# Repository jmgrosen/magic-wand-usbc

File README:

the proprietary charger for the rechargeable magic wand is pretty annoying, isn't it? this is a dongle that lets you charge it with any 15W USB-C charger instead!

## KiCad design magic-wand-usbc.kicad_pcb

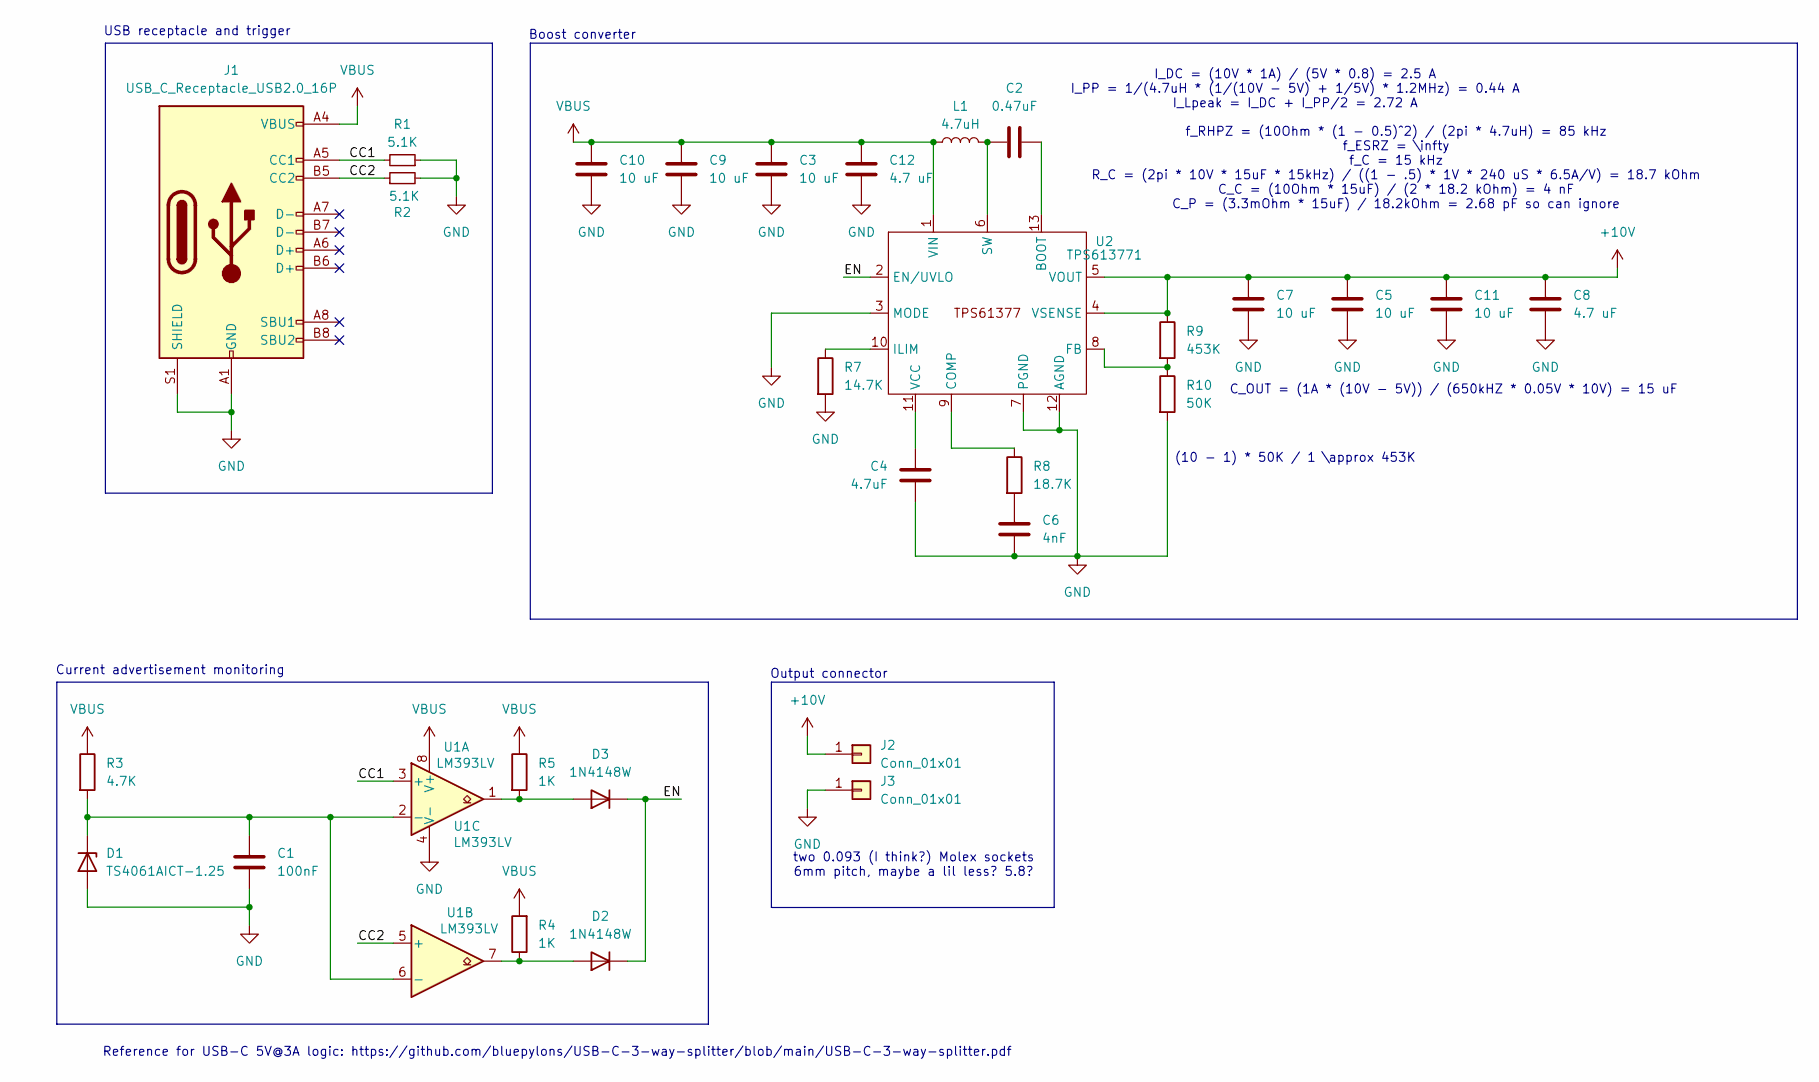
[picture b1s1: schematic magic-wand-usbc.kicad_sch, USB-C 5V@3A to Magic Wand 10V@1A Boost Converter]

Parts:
C1: 100nF; C_0402_1005Metric; DigiKey Part Number 1276-1043-1-ND
C2: 0.47uF; C_0402_1005Metric; DigiKey Part Number 311-1735-1-ND
C3, C5, C7, C9, C10, C11: 10 uF; C_0805_2012Metric; DigiKey Part Number 490-10514-1-ND
C4: 4.7uF; C_0402_1005Metric; DigiKey Part Number 490-GRM155C61E475ME15DCT-ND
C6: 4nF; C_0402_1005Metric; DigiKey Part Number 490-GCM155R71H392KA37DCT-ND
C8, C12: 4.7 uF; C_0402_1005Metric; DigiKey Part Number 490-GRM155C61E475ME15DCT-ND
D1: TS4061AICT-1.25; SOT-323_SC-70; DigiKey Part Number 497-15220-1-ND
D2, D3: 1N4148W; D_SOD-523; DigiKey Part Number 1N4148WTDICT-ND
J1: USB_C_Receptacle_USB2.0_16P; USB_C_Receptacle_GCT_USB4105-xx-A_16P_TopMnt_Horizontal; DigiKey Part Number 2073-USB4105-GF-ACT-ND
J2, J3: Conn_01x01; Molex_Socket_Janky
L1: 4.7uH; IND_SRP4030FA_BRN; Part Number SRP4030FA-4R7M; DigiKey Part Number SRP4030FA-4R7MCT-ND
R1, R2: 5.1K; R_0402_1005Metric; DigiKey Part Number 13-RC0402FR-135K1LCT-ND
R3: 4.7K; R_0402_1005Metric; DigiKey Part Number 311-4.7KLRCT-ND
R4, R5: 1K; R_0402_1005Metric; DigiKey Part Number 311-1.00KLRCT-ND
R7: 14.7K; R_0402_1005Metric; DigiKey Part Number YAG5262CT-ND
R8: 18.7K; R_0402_1005Metric; DigiKey Part Number YAG3018CT-ND
R9: 453K; R_0402_1005Metric; DigiKey Part Number YAG3164CT-ND
R10: 50K; R_0402_1005Metric; DigiKey Part Number 541-CRCW040250K0FKEDCT-ND
U1: LM393LV; WSON8_DSG_TEX; Part Number LM393LVDSGR; DigiKey Part Number 296-LM393LVDSGRCT-ND
U2: TPS613771; TPS61377-VQFN-HR13; DigiKey Part Number 296-TPS613771RYHRCT-ND

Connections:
+10V: C5.1, C7.1, C8.1, C11.1, J2.1, R9.1, U2.4 (VSENSE), U2.5 (VOUT)
/CC1: J1.A5 (CC1), R1.2, U1.3 (+)
/CC2: J1.B5 (CC2), R2.1, U1.5 (+)
/EN: D2.1 (K), D3.1 (K), U2.2 (EN/UVLO)
GND: C1.2, C3.2, C4.1, C5.2, C6.2, C7.2, C8.2, C9.2, C10.2, C11.2, C12.2, D1.2 (A), J1.A1 (GND), J1.A12 (GND), J1.B1 (GND), J1.B12 (GND), J1.S1 (SHIELD), J3.1, R1.1, R2.2, R7.2, R10.2, U1.4 (V-), U2.3 (MODE), U2.7 (PGND), U2.12 (AGND)
unnamed: C6.1, R8.2
unnamed: C1.1, D1.1 (K), R3.2, U1.2 (-), U1.6 (-)
unnamed: D2.2 (A), R4.1, U1.7
unnamed: D3.2 (A), R5.2, U1.1
unnamed: C2.2, U2.13 (BOOT)
unnamed: R8.1, U2.9 (COMP)
unnamed: R9.2, R10.1, U2.8 (FB)
unnamed: R7.1, U2.10 (ILIM)
unnamed: C2.1, L1.2, U2.6 (SW)
unnamed: C4.2, U2.11 (VCC)
VBUS: C3.1, C9.1, C10.1, C12.1, J1.A4 (VBUS), J1.A9 (VBUS), J1.B4 (VBUS), J1.B9 (VBUS), L1.1, R3.1, R4.2, R5.1, U1.8 (V+), U2.1 (VIN)

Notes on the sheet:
Reference for USB-C 5V@3A logic: https://github.com/bluepylons/USB-C-3-way-splitter/blob/main/USB-C-3-way-splitter.pdf
two 0.093 (I think?) Molex sockets 6mm pitch, maybe a lil less? 5.8?
(10 - 1) * 50K / 1 \approx 453K
f_RHPZ = (10Ohm * (1 - 0.5)^2) / (2pi * 4.7uH) = 85 kHz f_ESRZ = \infty f_C = 15 kHz R_C = (2pi * 10V * 15uF * 15kHz) / ((1 - .5) * 1V * 240 uS * 6.5A/V) = 18.7 kOhm C_C = (10Ohm * 15uF) / (2 * 18.2 kOhm) = 4 nF C_P = (3.3mOhm * 15uF) / 18.2kOhm = 2.68 pF so can ignore
Output connector
C_OUT = (1A * (10V - 5V)) / (650kHZ * 0.05V * 10V) = 15 uF
I_DC = (10V * 1A) / (5V * 0.8) = 2.5 A I_PP = 1/(4.7uH * (1/(10V - 5V) + 1/5V) * 1.2MHz) = 0.44 A I_Lpeak = I_DC + I_PP/2 = 2.72 A
Current advertisement monitoring
Boost converter
USB receptacle and trigger

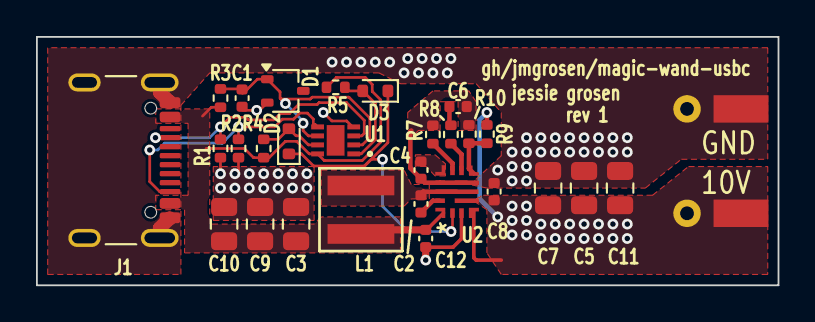
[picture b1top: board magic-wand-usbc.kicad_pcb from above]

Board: 2 copper layers, 41.2 x 13.8 mm, 30 parts (0 on the bottom side), 16 nets.

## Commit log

2025-06-07 initial version
2025-07-09 update to kicad 9
